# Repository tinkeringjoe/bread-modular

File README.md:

# Bread Modular
Bread Modular is an open-source hardware modular synthesizer format designed to be minimalistic and cost-effective.

### Key Features

* **Modular Design:** Just like Eurorack
* **USB-Powered:** It can be portable
* **Minimal Design:** Cost Effective
* **Modular MIDI Support:** Use MIDI to communicate between modules (still supports CV & Gate)
* **Analog and Digital Signal Paths:** It’s your choice 
* **Diverse Built-in Modules:** Includes a wide range of pre-designed modules
* **Configurable Digital Modules:** Supports both voice and CV (uses AtTiny 1616 or ESP32)
* **Fully Open Source:** Including schematics, PCB designs, and code
* **Ease of Customization:** Enables straightforward creation of custom modules tailored to specific needs.
* **No Case Required:** Can be used directly on a breadboard or mounted on a simple base module.

## Table of Contents

* [Specification](https://github.com/bread-modular/bread-modular/wiki/Specification)
* [Common Parts](https://github.com/bread-modular/bread-modular/wiki/Common-Parts)
* [Modules](https://github.com/bread-modular/bread-modular/wiki/Modules)

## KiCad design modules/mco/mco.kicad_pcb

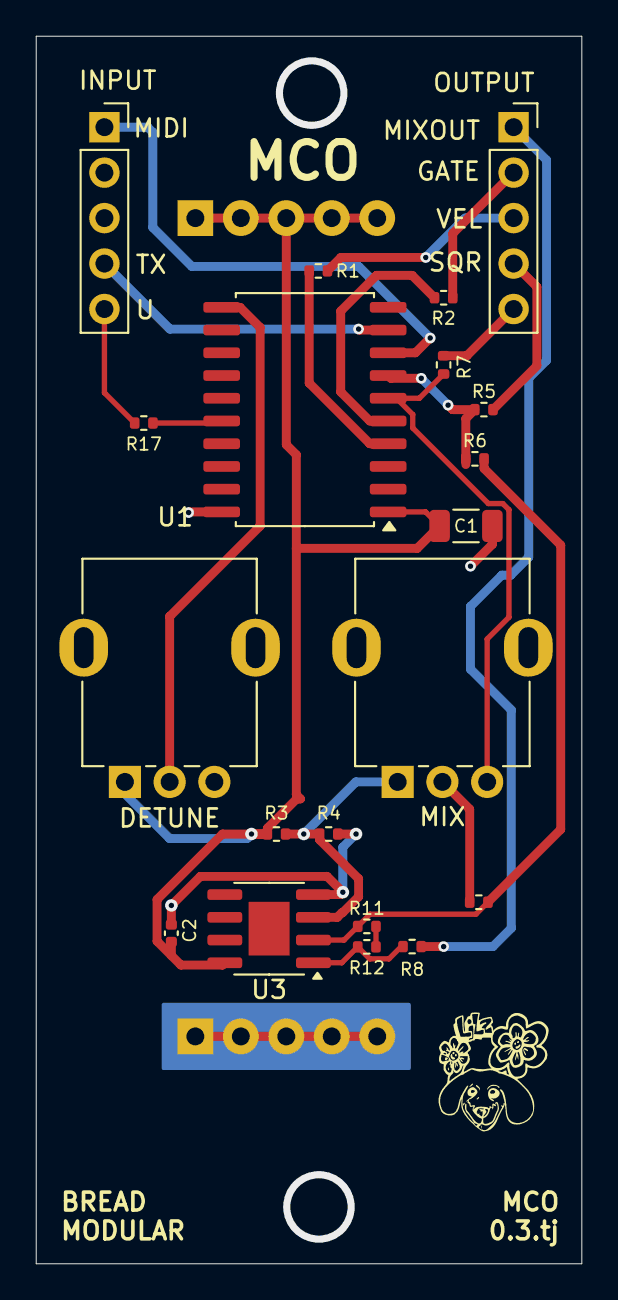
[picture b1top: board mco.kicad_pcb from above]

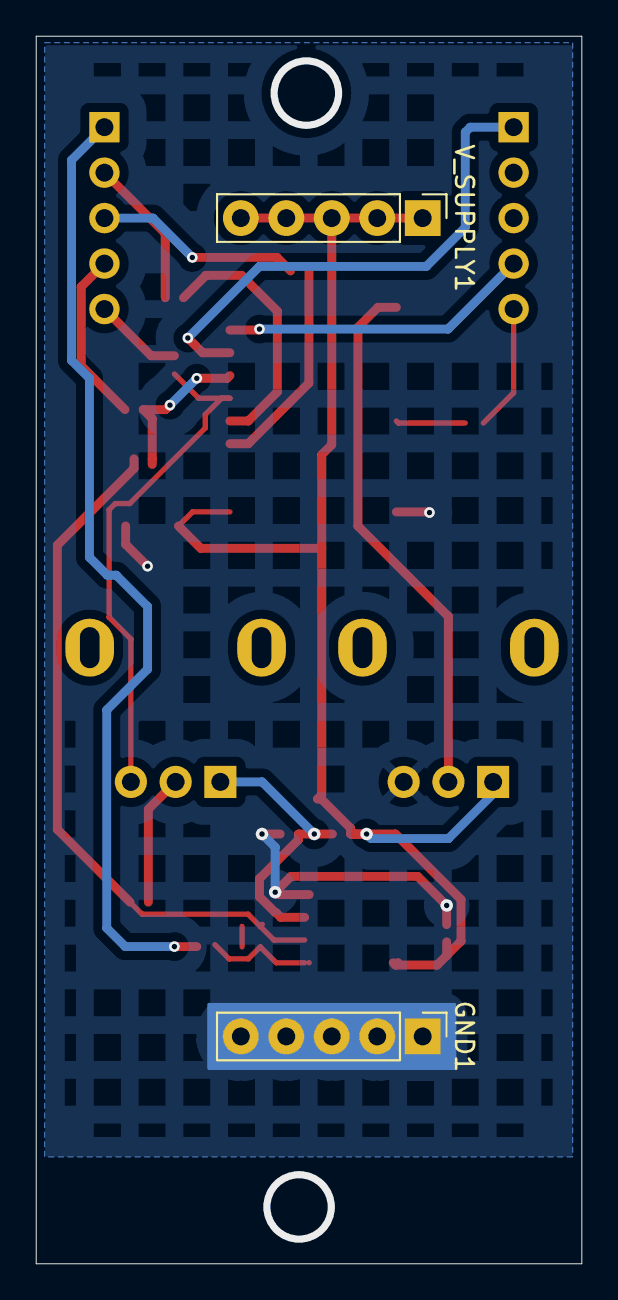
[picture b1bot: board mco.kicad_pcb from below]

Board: 2 copper layers, 30.5 x 68.6 mm, 22 parts (2 on the bottom side), 21 nets.

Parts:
C1: 100uf; C_1206_3216Metric
C2: 0.1uf; C_0402_1005Metric
GND1: Conn_01x05_Pin; Power_Connector
INPUT1: Conn_01x05_Socket; PinSocket_1x05_P2.54mm_Vertical
OUTPUT1: Conn_01x05_Socket; PinSocket_1x05_P2.54mm_Vertical
R1, R2, R3, R4, R5, R7, R8: 1k; R_0402_1005Metric
R6, R10: 1M; R_0402_1005Metric
R11, R12: 200k; R_0402_1005Metric
R17: 4.7k; R_0402_1005Metric
RV1, RV2: 50k; Potentiometer_RV09
U1: ATtiny1616-S; SOIC-20W_7.5x12.8mm_P1.27mm
U3: MCP6002-xSN; SOIC-8-1EP_3.9x4.9mm_P1.27mm_EP2.29x3mm
V_SUPPLY1: Conn_01x05_Pin; Power_Connector

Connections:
DETUNED_OUT: OUTPUT1.5, R7.2
DETUNED_TONE: R7.1, RV2.3, U1.6 (PB5)
FUNDAMENTAL_TONE: R5.1, R6.1, U1.7 (PB4)
GATE: OUTPUT1.2, R2.2
GND: C1.1, C2.2, GND1.1, GND1.2, GND1.3, GND1.4, GND1.5, R4.2, RV1.3, U1.20 (GND), U3.4 (V-)
MIDI: INPUT1.1, U1.8 (PB3)
MIX_OUT: OUTPUT1.1, R8.2
unnamed: R10.1, RV2.2
unnamed: R11.2, R12.1
unnamed: R8.1, R12.2, U3.1
unnamed: R1.1, U1.4 (PA6)
unnamed: R2.1, U1.5 (PA7)
unnamed: R17.1, U1.16 (~RESET/PA0)
unnamed: R6.2, R10.2, R11.1, U3.2 (-)
SQUARE_OUT: OUTPUT1.4, R5.2
TX: INPUT1.4, U1.9 (PB2)
UDPI: INPUT1.5, R17.2
VELOCITY: OUTPUT1.3, R1.2
V_DETUNED: RV1.2, U1.11 (PB0)
V_MID: R3.2, R4.1, RV2.1, U3.3 (+)
V_SUPPLY: C1.2, C2.1, R3.1, RV1.1, U1.1 (VCC), U3.8 (V+), V_SUPPLY1.1, V_SUPPLY1.2, V_SUPPLY1.3, V_SUPPLY1.4, V_SUPPLY1.5

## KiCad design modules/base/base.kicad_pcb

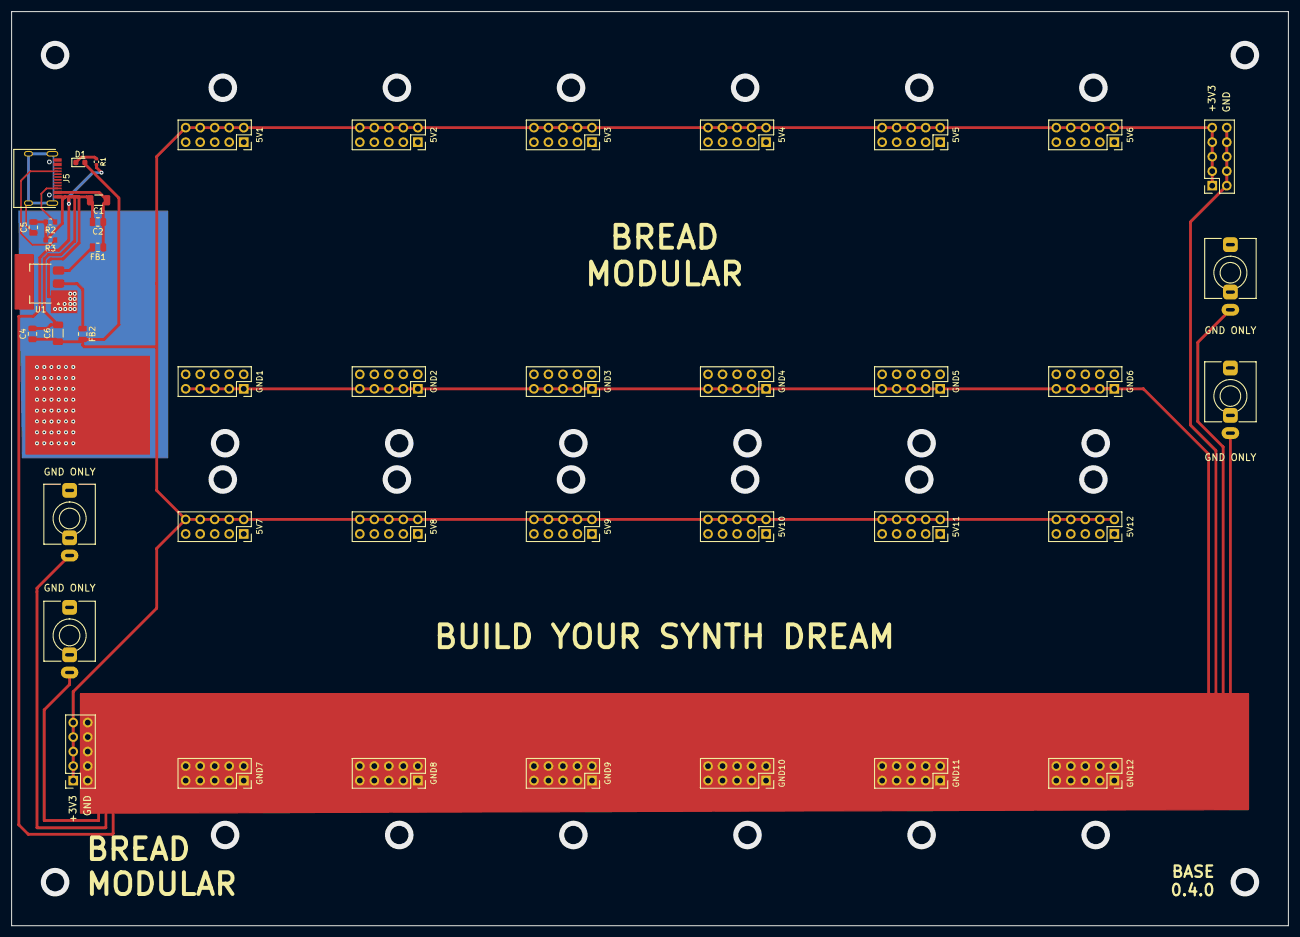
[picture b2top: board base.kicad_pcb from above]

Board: 2 copper layers, 223.5 x 160.0 mm, 43 parts (0 on the bottom side), 9 nets.

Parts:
5V1, 5V2, 5V3, 5V4, 5V5, 5V6, 5V7, 5V8, 5V9, 5V10, 5V11, 5V12, 5V13, 5V14: Conn_02x05_Socket; PinSocket_2x05_P2.54mm_Vertical
C1, C6: 100uf; C_1206_3216Metric
C2, C4: 0.1uf; C_0805_2012Metric
C5: 10nf; C_0805_2012Metric
D1: LED; LED_0603_1608Metric
FB1, FB2: GZ2012E800TF; C_0805_2012Metric
GND1, GND2, GND3, GND4, GND5, GND6, GND7, GND8, GND9, GND10, GND11, GND12: Conn_02x05_Socket; PinSocket_2x05_P2.54mm_Vertical
J1, J2, J3, J4: Ground; Jack_3.5mm_QingPu_WQP-PJ366ST_Vertical
J5: USB_C_Receptacle_PowerOnly_6P; HRO-TYPE-C-31-M-12
R1: 1k; R_0402_1005Metric
R2, R3: 5.1k; R_0603_1608Metric
U1: AMS1117-3.3; SOT-223

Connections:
+3.3V: 5V1.2, 5V1.4, 5V1.6, 5V1.8, 5V1.10, 5V2.2, 5V2.4, 5V2.6, 5V2.8, 5V2.10, 5V3.2, 5V3.4, 5V3.6, 5V3.8, 5V3.10, 5V4.2, 5V4.4, 5V4.6, 5V4.8, 5V4.10, 5V5.2, 5V5.4, 5V5.6, 5V5.8, 5V5.10, 5V6.2, 5V6.4, 5V6.6, 5V6.8, 5V6.10, 5V7.2, 5V7.4, 5V7.6, 5V7.8, 5V7.10, 5V8.2, 5V8.4, 5V8.6, 5V8.8, 5V8.10, 5V9.2, 5V9.4, 5V9.6, 5V9.8, 5V9.10, 5V10.2, 5V10.4, 5V10.6, 5V10.8, 5V10.10, 5V11.2, 5V11.4, 5V11.6, 5V11.8, 5V11.10, 5V12.2, 5V12.4, 5V12.6, 5V12.8, 5V12.10, 5V13.1, 5V13.3, 5V13.5, 5V13.7, 5V13.9, 5V14.1, 5V14.3, 5V14.5, 5V14.7, 5V14.9, C4.1, C6.1, D1.2 (A), FB2.2
+5V: C1.1, C2.1, FB1.1, J5.A9 (VBUS)
GND: 5V13.2, 5V13.4, 5V13.6, 5V13.8, 5V13.10, 5V14.2, 5V14.4, 5V14.6, 5V14.8, 5V14.10, C1.2, C2.2, C4.2, C5.2, C6.2, GND1.1, GND1.3, GND1.5, GND1.7, GND1.9, GND2.1, GND2.3, GND2.5, GND2.7, GND2.9, GND3.1, GND3.3, GND3.5, GND3.7, GND3.9, GND4.1, GND4.3, GND4.5, GND4.7, GND4.9, GND5.1, GND5.3, GND5.5, GND5.7, GND5.9, GND6.1, GND6.3, GND6.5, GND6.7, GND6.9, GND7.1, GND7.2, GND7.3, GND7.4, GND7.5, GND7.6, GND7.7, GND7.8, GND7.9, GND7.10, GND8.1, GND8.2, GND8.3, GND8.4, GND8.5, GND8.6, GND8.7, GND8.8, GND8.9, GND8.10, GND9.1, GND9.2, GND9.3, GND9.4, GND9.5, GND9.6, GND9.7, GND9.8, GND9.9, GND9.10, GND10.1, GND10.2, GND10.3, GND10.4, GND10.5, GND10.6, GND10.7, GND10.8, GND10.9, GND10.10, GND11.1, GND11.2, GND11.3, GND11.4, GND11.5, GND11.6, GND11.7, GND11.8, GND11.9, GND11.10, GND12.1, GND12.2, GND12.3, GND12.4, GND12.5, GND12.6, GND12.7, GND12.8, GND12.9, GND12.10, J1.S, J2.S, J3.S, J4.S, J5.A12 (GND), R1.2, R2.2, R3.2, U1.1 (GND)
unnamed: D1.1 (K), R1.1
unnamed: J5.A5 (CC1), R3.1
unnamed: J5.B5 (CC2), R2.1
unnamed: C5.1, J5.S1 (SHIELD)
unnamed: FB1.2, U1.3 (VI)
unnamed: FB2.1, U1.2 (VO)

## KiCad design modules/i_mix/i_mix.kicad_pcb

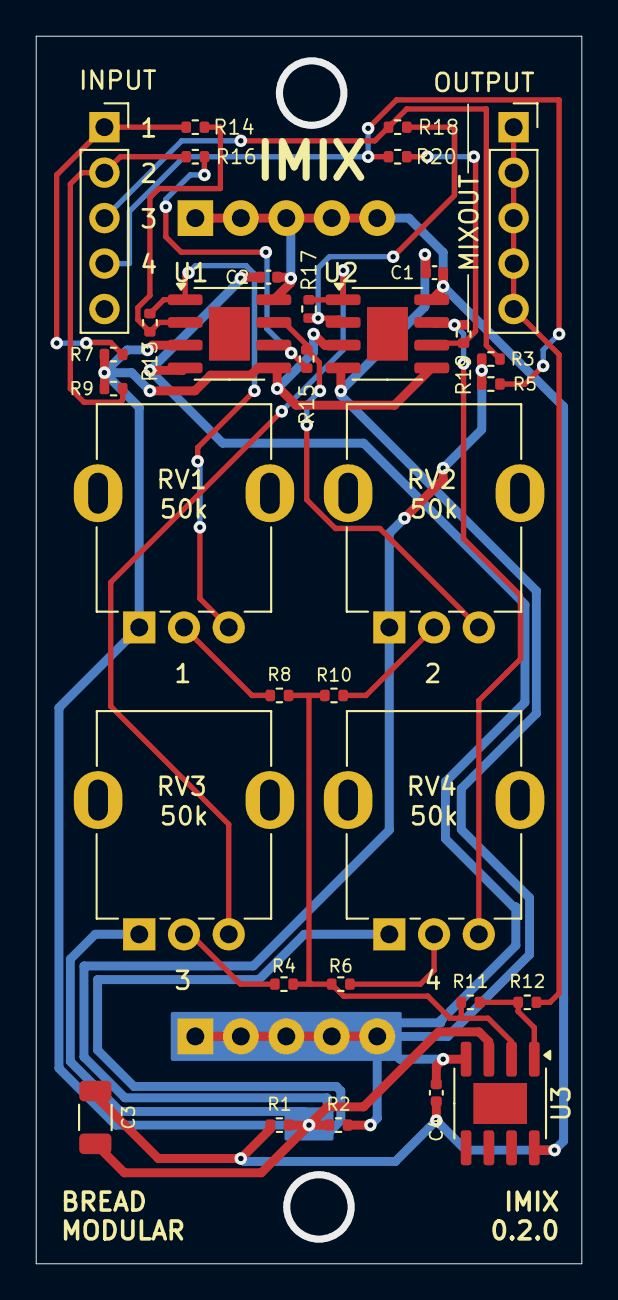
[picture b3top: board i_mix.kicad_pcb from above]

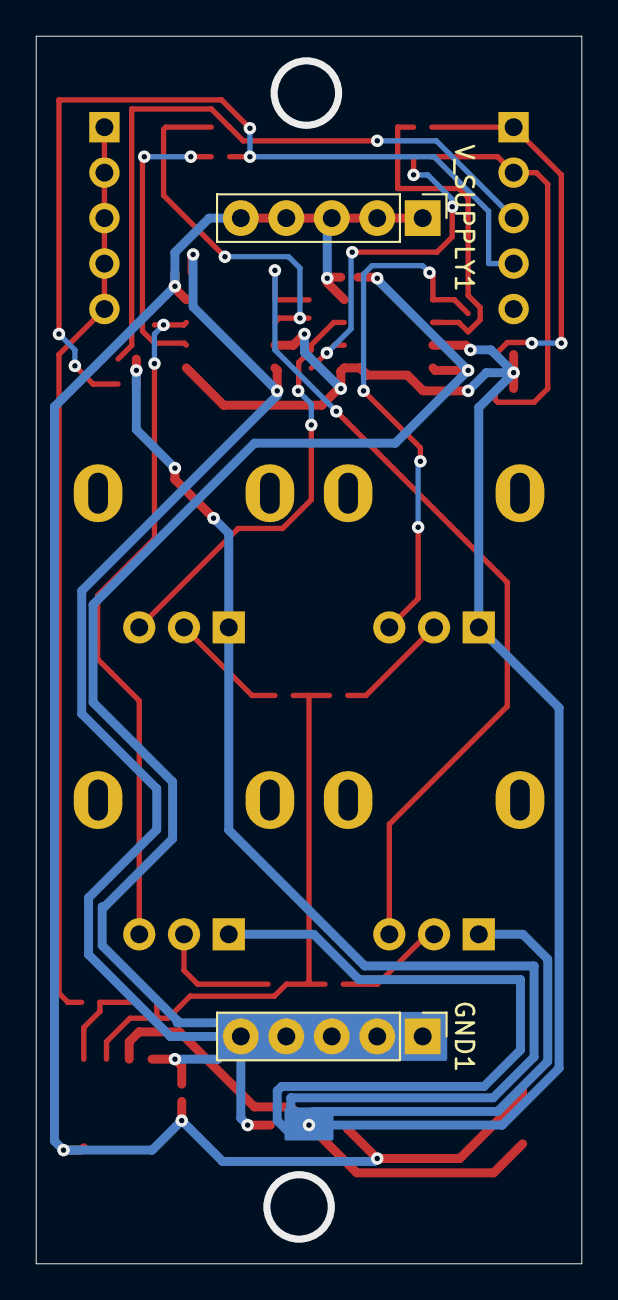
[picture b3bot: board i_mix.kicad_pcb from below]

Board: 2 copper layers, 30.5 x 68.6 mm, 35 parts (2 on the bottom side), 22 nets.

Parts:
C1, C2, C4: 0.1uf; C_0402_1005Metric
C3: 100uf; C_1206_3216Metric
GND1: Conn_01x05_Pin; Power_Connector
INPUT1: Conn_01x05_Socket; PinSocket_1x05_P2.54mm_Vertical
OUTPUT1: Conn_01x05_Socket; PinSocket_1x05_P2.54mm_Vertical
R1, R2, R12: 1k; R_0402_1005Metric
R3, R5, R7, R9: 1M; R_0402_1005Metric
R4, R6, R8, R10, R11: 200k; R_0402_1005Metric
R13, R14, R15, R16, R17, R18, R19, R20: 100k; R_0402_1005Metric
RV1, RV2, RV3, RV4: 50k; Potentiometer_RV09
U1, U2, U3: MCP6002-xSN; SOIC-8-1EP_3.9x4.9mm_P1.27mm_EP2.29x3mm
V_SUPPLY1: Conn_01x05_Pin; Power_Connector

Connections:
GND: C1.2, C2.2, C4.2, GND1.1, GND1.2, GND1.3, GND1.4, GND1.5, R2.2, U1.4 (V-), U2.4 (V-), U3.4 (V-)
IN_1: INPUT1.1, R7.2, R14.1
IN_2: INPUT1.2, R9.2, R16.1
IN_3: INPUT1.3, R3.2, R18.1
IN_4: INPUT1.4, R5.2, R20.1
MIXOUT: OUTPUT1.1, OUTPUT1.2, OUTPUT1.3, OUTPUT1.4, OUTPUT1.5, R12.2
unnamed: R4.1, RV3.2
unnamed: R6.1, RV4.2
unnamed: R8.1, RV1.2
unnamed: R10.1, RV2.2
unnamed: R11.2, R12.1, U3.1
unnamed: R13.2, RV1.3, U1.1
unnamed: R15.2, RV2.3, U1.7
unnamed: R17.2, RV3.3, U2.1
unnamed: R19.2, RV4.3, U2.7
unnamed: R13.1, R14.2, U1.2 (-)
unnamed: R15.1, R16.2, U1.6 (-)
unnamed: R17.1, R18.2, U2.2 (-)
unnamed: R19.1, R20.2, U2.6 (-)
unnamed: R4.2, R6.2, R8.2, R10.2, R11.1, U3.2 (-)
V_MID: C3.2, R1.2, R2.1, R3.1, R5.1, R7.1, R9.1, RV1.1, RV2.1, RV3.1, RV4.1, U1.3 (+), U1.5 (+), U2.3 (+), U2.5 (+), U3.3 (+)
V_SUPPLY: C1.1, C2.1, C3.1, C4.1, R1.1, U1.8 (V+), U2.8 (V+), U3.8 (V+), V_SUPPLY1.1, V_SUPPLY1.2, V_SUPPLY1.3, V_SUPPLY1.4, V_SUPPLY1.5

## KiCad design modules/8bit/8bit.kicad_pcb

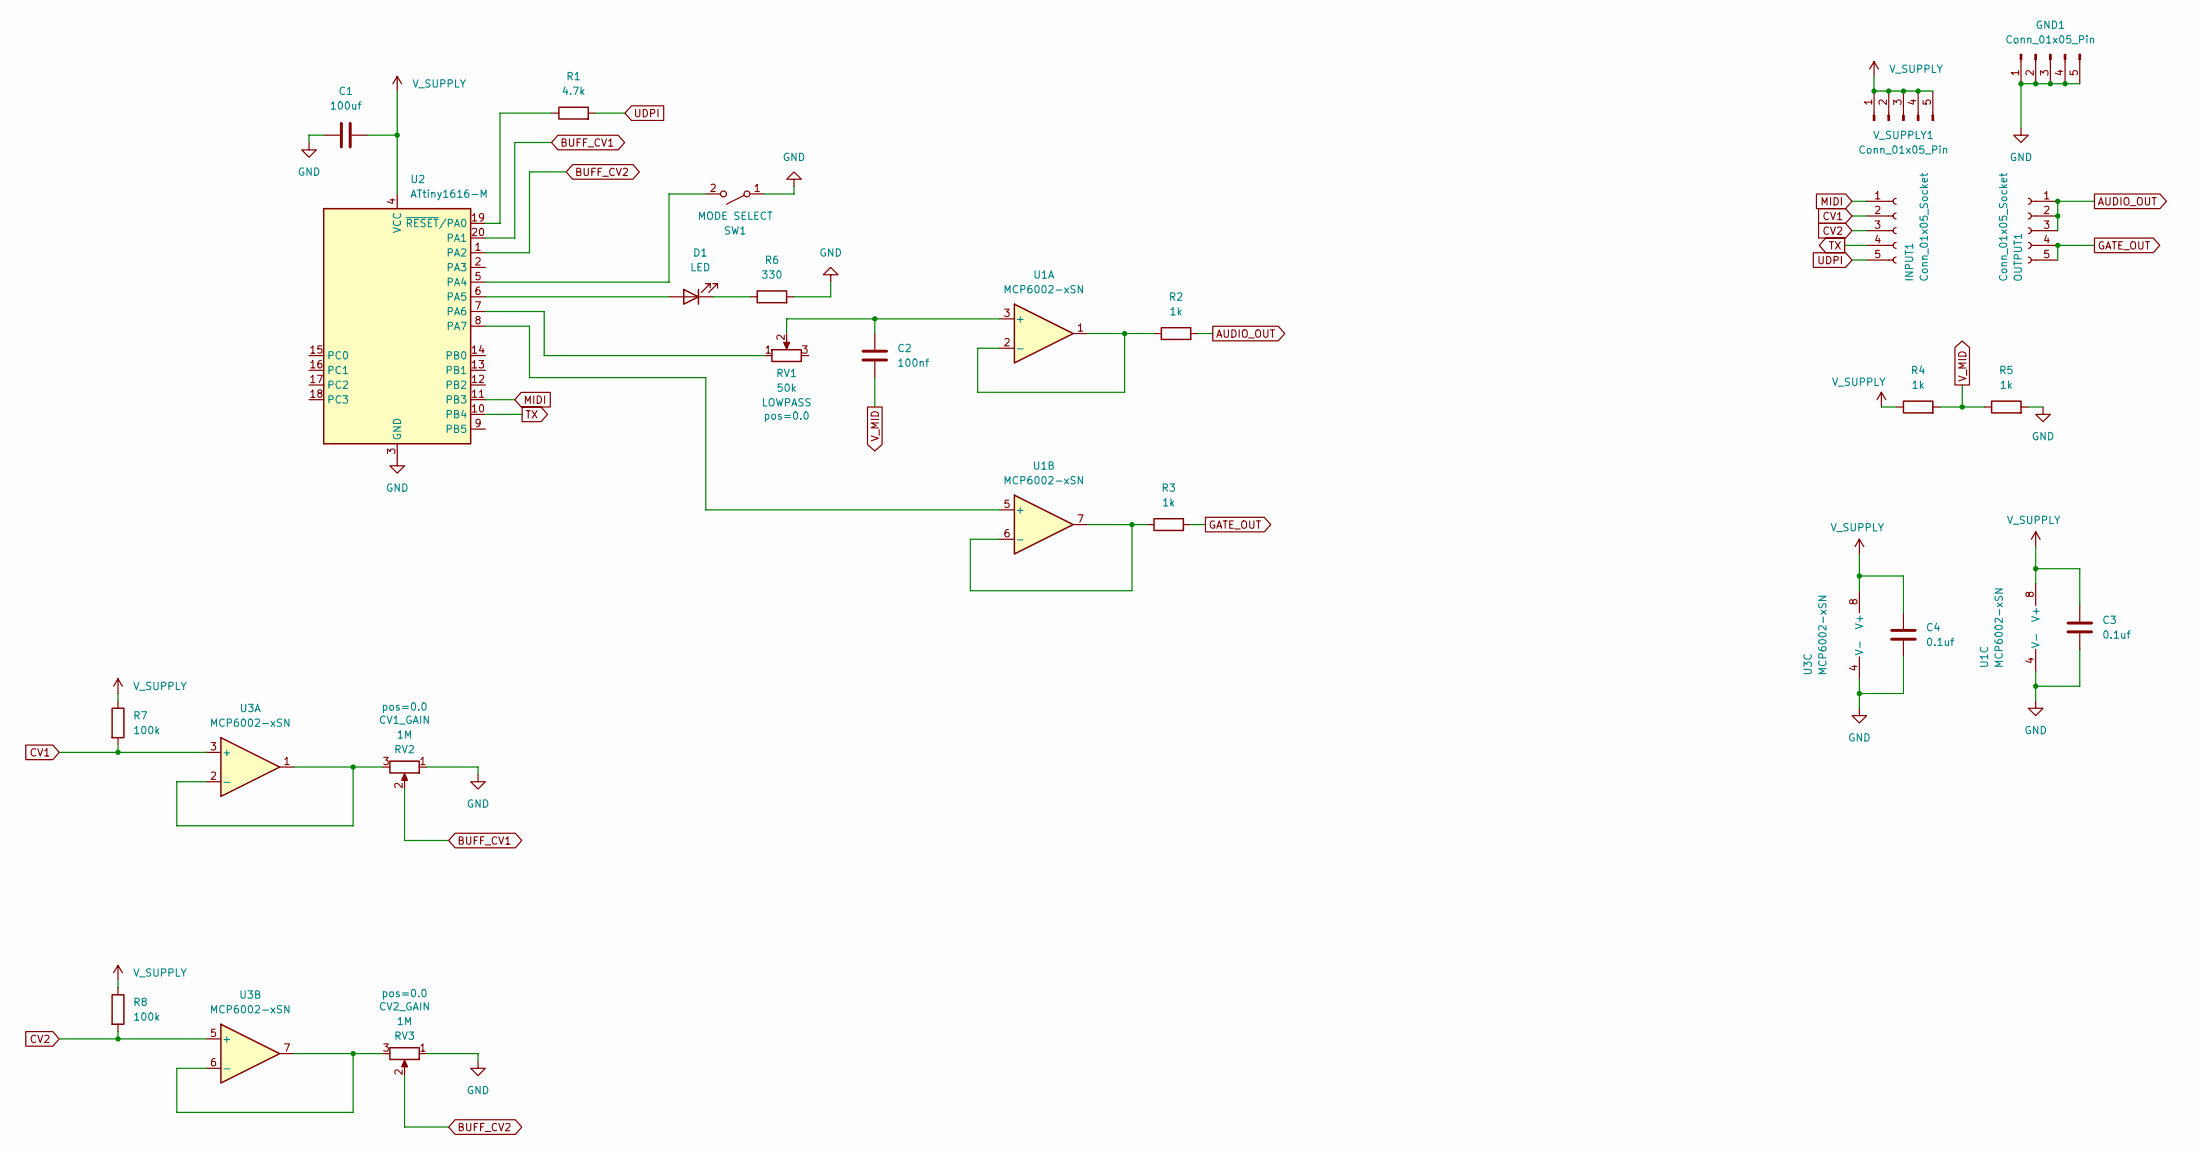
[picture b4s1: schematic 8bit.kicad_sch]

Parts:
C1: 100uf; C_1206_3216Metric
C2: 100nf; C_0402_1005Metric
C3, C4: 0.1uf; C_0402_1005Metric
D1: LED; LED_0603_1608Metric
GND1: Conn_01x05_Pin; Power_Connector
INPUT1: Conn_01x05_Socket; PinSocket_1x05_P2.54mm_Vertical
OUTPUT1: Conn_01x05_Socket; PinSocket_1x05_P2.54mm_Vertical
R1: 4.7k; R_0402_1005Metric
R2, R3, R4, R5: 1k; R_0402_1005Metric
R6: 330; R_0402_1005Metric
R7, R8: 100k; R_0402_1005Metric
RV1: 50k; Potentiometer_RV09
RV2, RV3: 1M; Potentiometer_RV09
SW1: MODE SELECT; SPST_TS-1187A-B-A-B
U1, U3: MCP6002-xSN; SOIC-8-1EP_3.9x4.9mm_P1.27mm_EP2.29x3mm
U2: ATtiny1616-M; VQFN-20-1EP_3x3mm_P0.4mm_EP1.7x1.7mm
V_SUPPLY1: Conn_01x05_Pin; Power_Connector

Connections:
AUDIO_OUT: OUTPUT1.1, OUTPUT1.2, OUTPUT1.3, R2.2
BUFF_CV1: RV2.2, U2.20 (PA1)
BUFF_CV2: RV3.2, U2.1 (PA2)
CV1: INPUT1.2, R7.2, U3.3 (+)
CV2: INPUT1.3, R8.2, U3.5 (+)
GATE_OUT: OUTPUT1.4, OUTPUT1.5, R3.2
GND: C1.1, C3.2, C4.2, GND1.1, GND1.2, GND1.3, GND1.4, GND1.5, R5.2, R6.2, RV2.1, RV3.1, SW1.1 (A), U1.4 (V-), U2.3 (GND), U2.21 (GND), U3.4 (V-)
MIDI: INPUT1.1, U2.11 (PB3)
unnamed: D1.2 (A), U2.6 (PA5)
unnamed: D1.1 (K), R6.1
unnamed: SW1.2 (B), U2.5 (PA4)
unnamed: C2.2, RV1.2, U1.3 (+)
unnamed: R2.1, U1.1, U1.2 (-)
unnamed: U1.5 (+), U2.8 (PA7)
unnamed: R3.1, U1.6 (-), U1.7
unnamed: RV1.1, U2.7 (PA6)
unnamed: R1.1, U2.19 (~RESET/PA0)
unnamed: RV2.3, U3.1, U3.2 (-)
unnamed: RV3.3, U3.6 (-), U3.7
TX: INPUT1.4, U2.10 (PB4)
UDPI: INPUT1.5, R1.2
V_MID: C2.1, R4.2, R5.1
V_SUPPLY: C1.2, C3.1, C4.1, R4.1, R7.1, R8.1, U1.8 (V+), U2.4 (VCC), U3.8 (V+), V_SUPPLY1.1, V_SUPPLY1.2, V_SUPPLY1.3, V_SUPPLY1.4, V_SUPPLY1.5

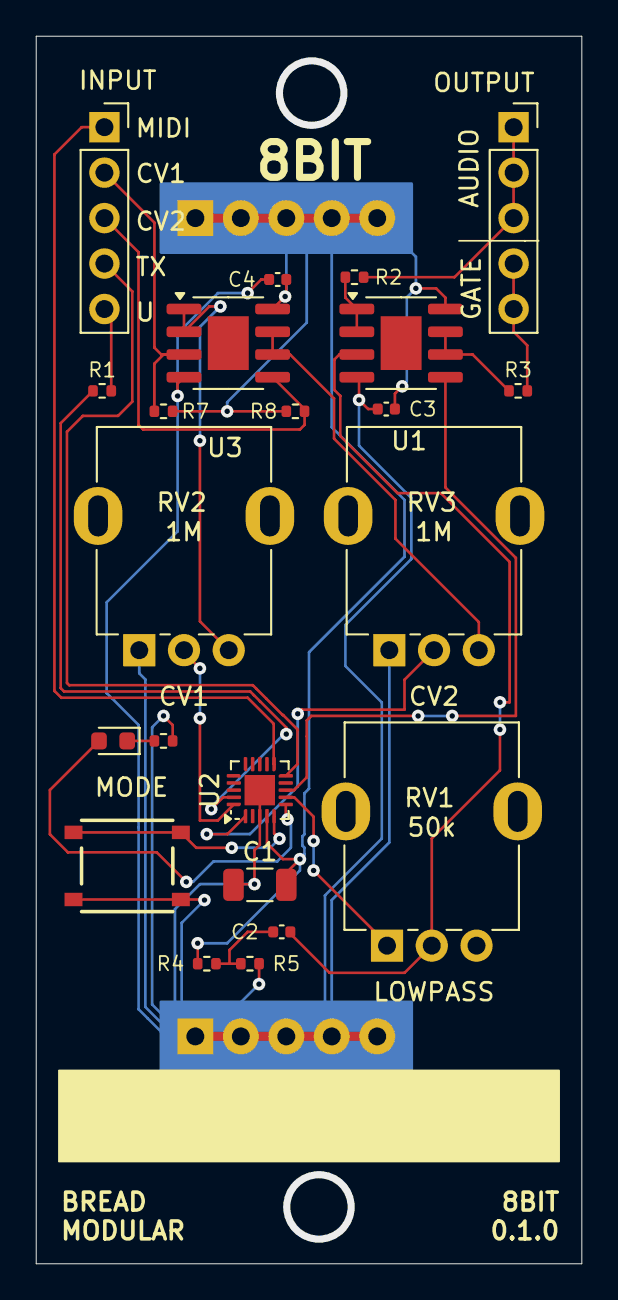
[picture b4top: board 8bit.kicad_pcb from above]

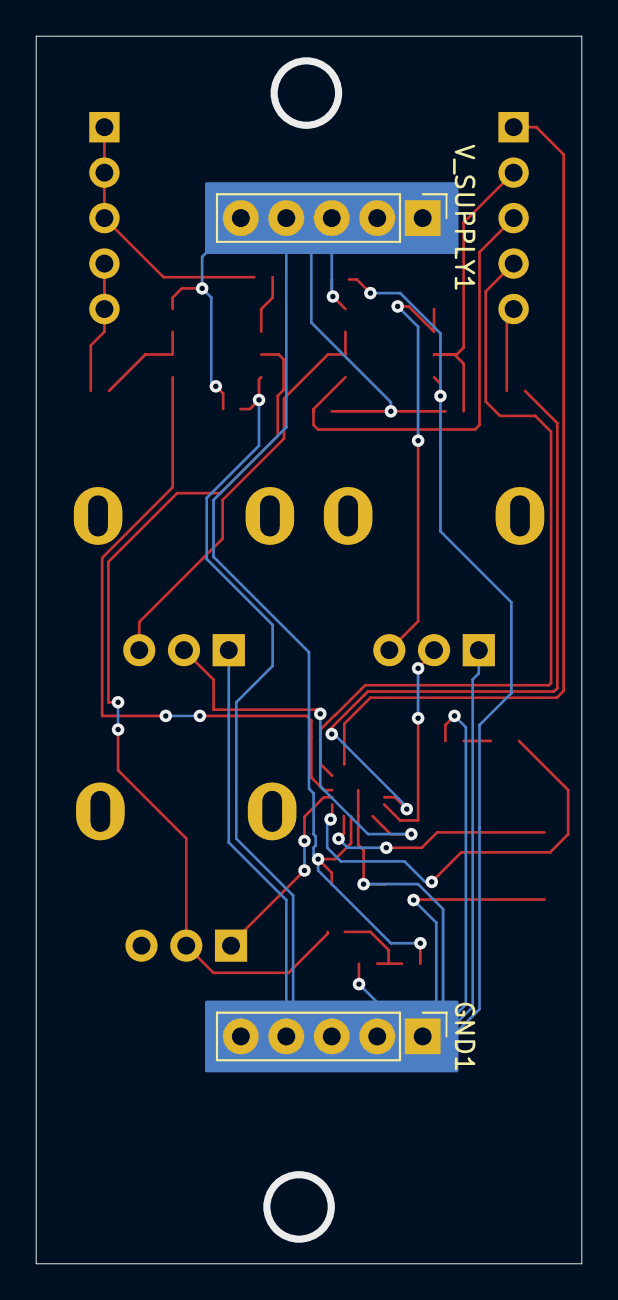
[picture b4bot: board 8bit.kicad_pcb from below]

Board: 2 copper layers, 30.5 x 68.6 mm, 24 parts (2 on the bottom side), 23 nets.

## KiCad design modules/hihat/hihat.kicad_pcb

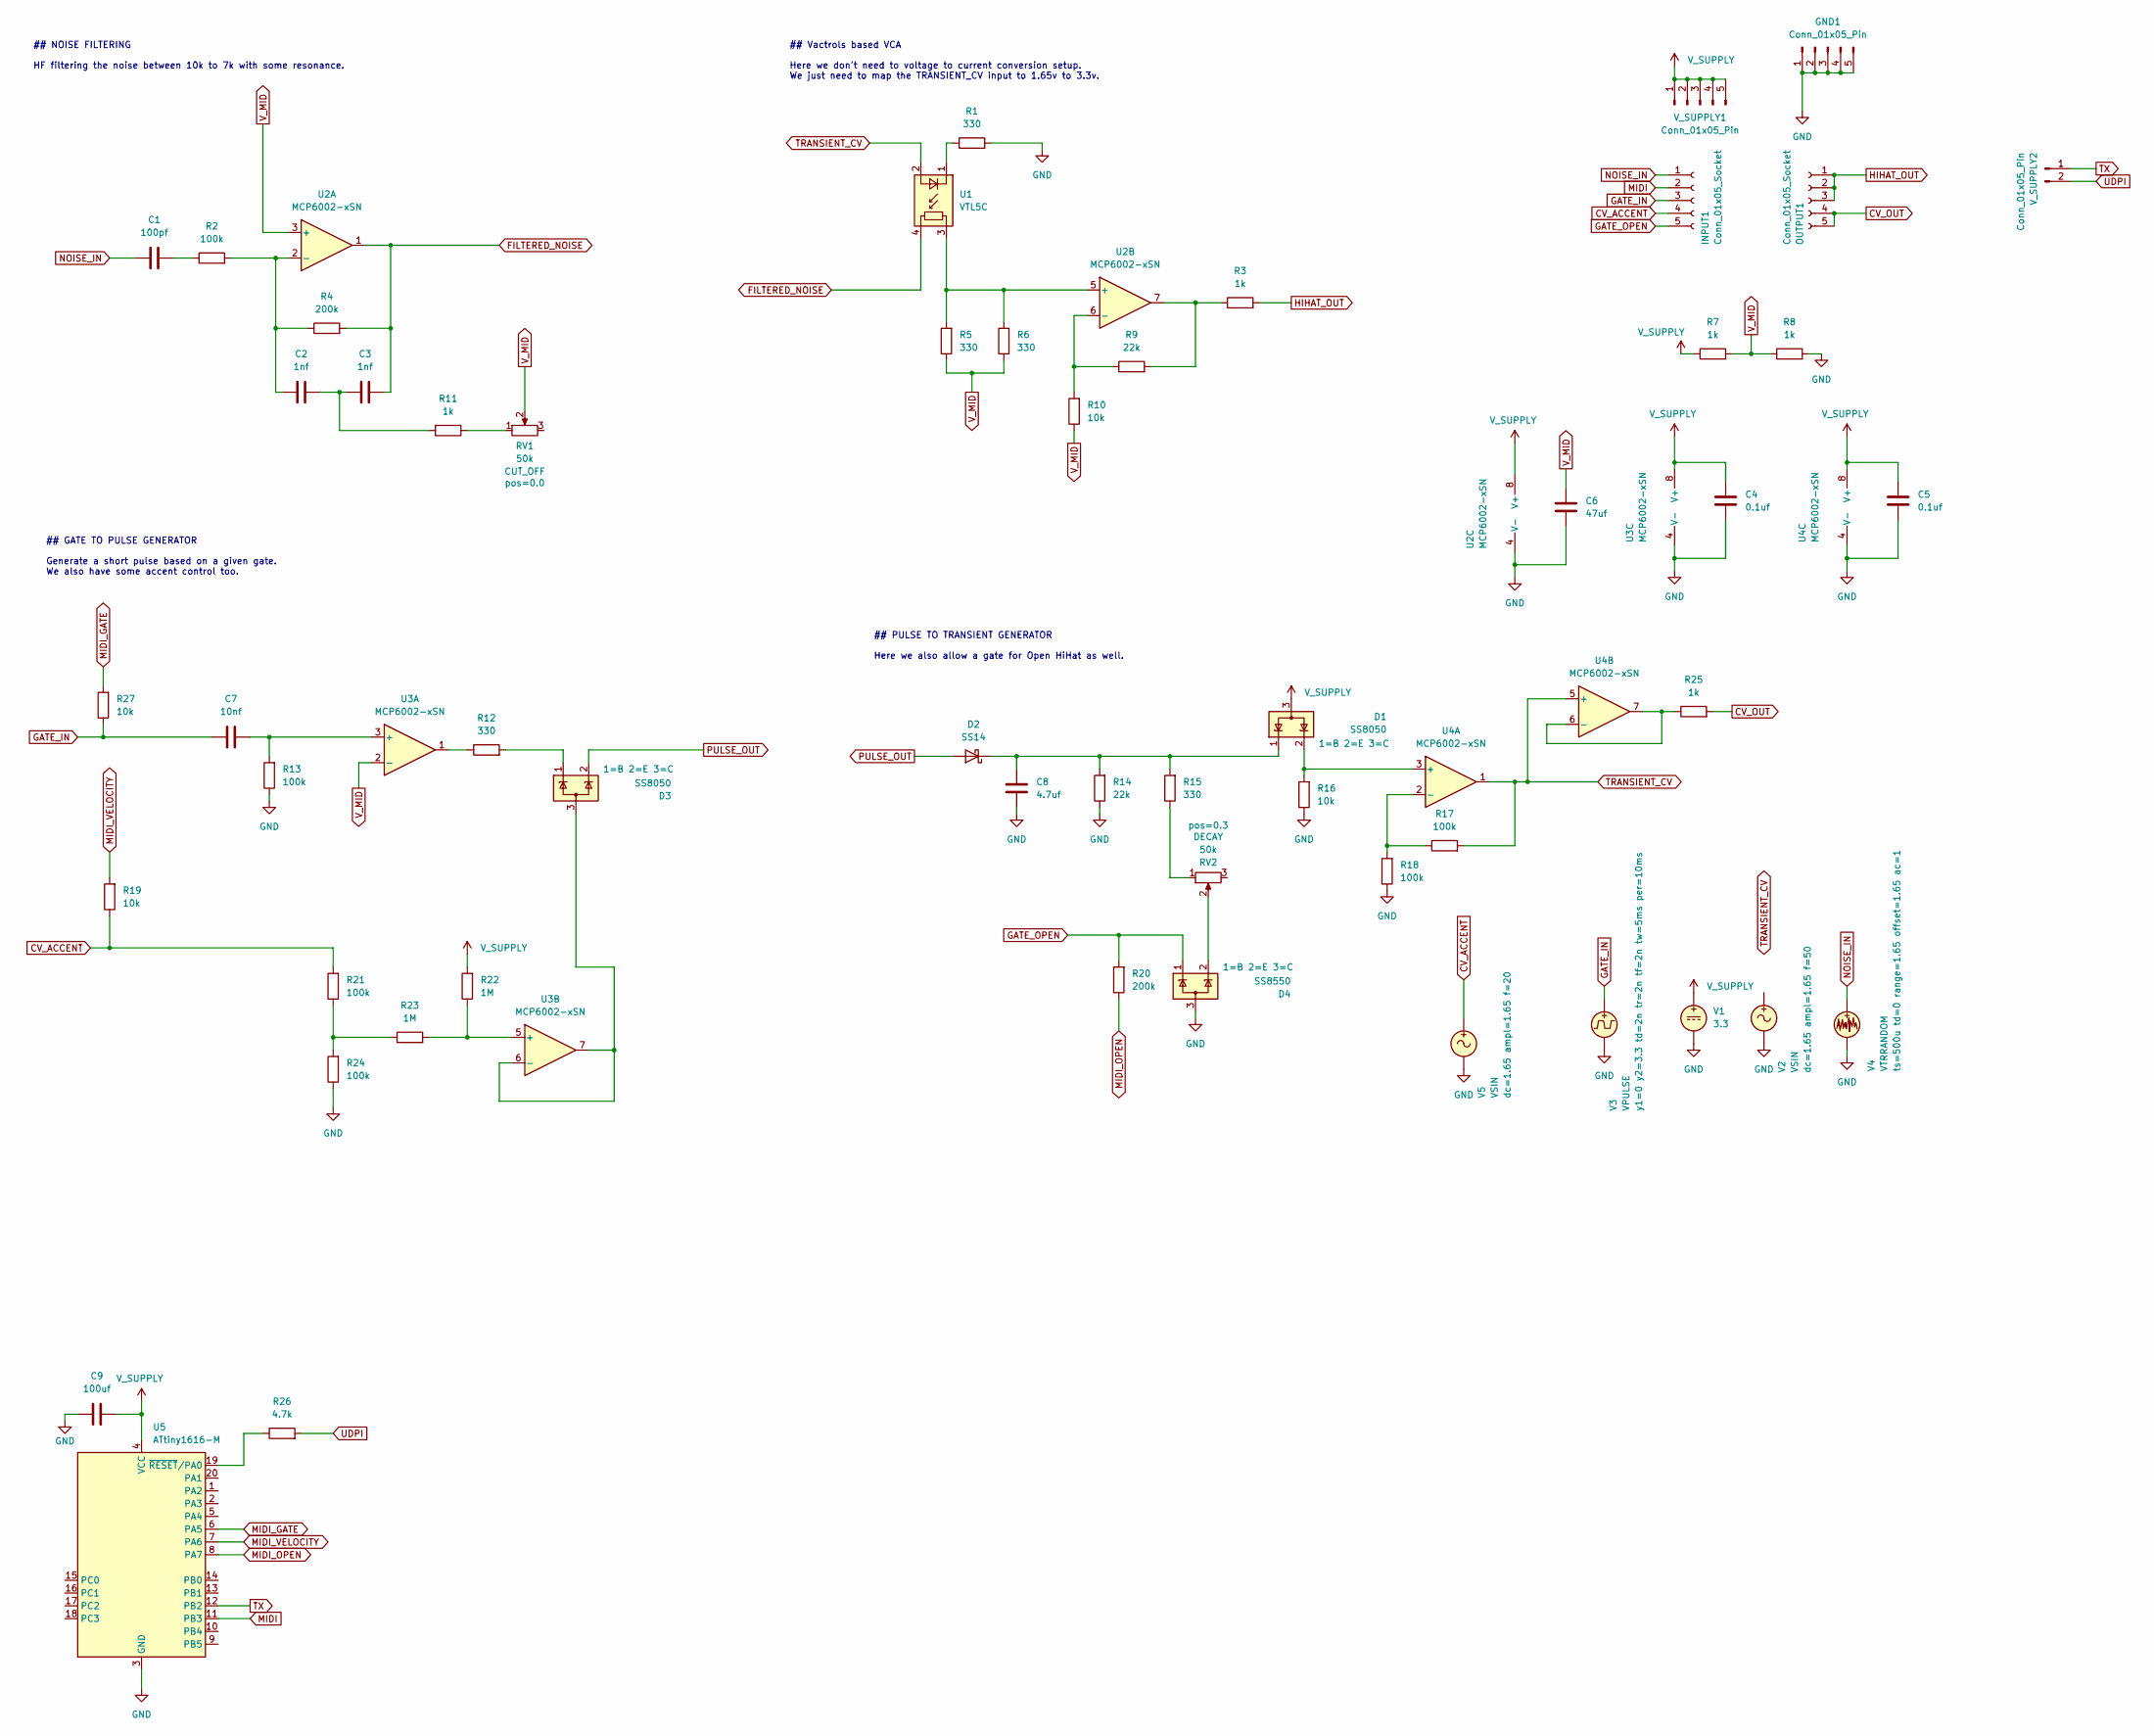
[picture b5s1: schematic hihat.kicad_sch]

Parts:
C1: 100pf; C_0402_1005Metric
C2, C3: 1nf; C_0402_1005Metric
C4, C5: 0.1uf; C_0402_1005Metric
C6: 47uf; C_0805_2012Metric
C7: 10nf; C_0402_1005Metric
C8: 4.7uf; C_0603_1608Metric
C9: 100uf; C_1206_3216Metric
D1, D3: SS8050; SOT-23
D2: SS14; D_SMA
D4: SS8550; SOT-23
GND1: Conn_01x05_Pin; Power_Connector
INPUT1: Conn_01x05_Socket; PinSocket_1x05_P2.54mm_Vertical
OUTPUT1: Conn_01x05_Socket; PinSocket_1x05_P2.54mm_Vertical
R1, R5, R6, R12, R15: 330; R_0402_1005Metric
R2, R13, R17, R18, R21, R24: 100k; R_0402_1005Metric
R3, R7, R8, R11, R25: 1k; R_0402_1005Metric
R4, R20: 200k; R_0402_1005Metric
R9, R14: 22k; R_0402_1005Metric
R10, R16, R19, R27: 10k; R_0402_1005Metric
R22, R23: 1M; R_0402_1005Metric
R26: 4.7k; R_0402_1005Metric
RV1, RV2: 50k; Potentiometer_RV09
U1: VTL5C
U2, U3, U4: MCP6002-xSN; SOIC-8-1EP_3.9x4.9mm_P1.27mm_EP2.29x3mm
U5: ATtiny1616-M; VQFN-20-1EP_3x3mm_P0.4mm_EP1.7x1.7mm
V1: 3.3
V2, V5: VSIN
V3: VPULSE
V4: VTRRANDOM
V_SUPPLY1: Conn_01x05_Pin; Power_Connector
V_SUPPLY2: Conn_01x05_Pin; Conn_Holes_2

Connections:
CV_ACCENT: INPUT1.4, R19.1, R21.2, V5.1
CV_OUT: OUTPUT1.4, OUTPUT1.5, R25.2
FILTERED_NOISE: C3.2, R4.2, U1.4, U2.1
GATE_IN: C7.1, INPUT1.3, R27.1, V3.1
GATE_OPEN: D4.1 (K), INPUT1.5, R20.2
GND: C4.1, C5.1, C6.1, C8.1, C9.1, D4.3 (A), GND1.1, GND1.2, GND1.3, GND1.4, GND1.5, R1.2, R8.2, R13.1, R14.1, R16.1, R18.1, R24.1, U2.4 (V-), U3.4 (V-), U4.4 (V-), U5.3 (GND), U5.21 (GND), V1.2, V2.2, V3.2, V4.2, V5.2
HIHAT_OUT: OUTPUT1.1, OUTPUT1.2, OUTPUT1.3, R3.2
MIDI: INPUT1.2, U5.11 (PB3)
MIDI_GATE: R27.2, U5.6 (PA5)
MIDI_OPEN: R20.1, U5.8 (PA7)
MIDI_VELOCITY: R19.2, U5.7 (PA6)
NOISE_IN: C1.1, INPUT1.1, V4.1
unnamed: C1.2, R2.1
unnamed: C2.2, C3.1, R11.2
unnamed: C8.2, D1.1 (K), D2.1 (K), R14.2, R15.2
unnamed: D3.3 (A), U3.6 (-), U3.7
unnamed: D3.1 (K), R12.2
unnamed: D4.2 (K), RV2.2
unnamed: R3.1, R9.2, U2.7
unnamed: R11.1, RV1.1
unnamed: R12.1, U3.1
unnamed: R15.1, RV2.1
unnamed: R21.1, R23.1, R24.2
unnamed: R1.1, U1.1 (-)
unnamed: C2.1, R2.2, R4.1, U2.2 (-)
unnamed: R5.2, R6.2, U1.3, U2.5 (+)
unnamed: R9.1, R10.2, U2.6 (-)
unnamed: C7.2, R13.2, U3.3 (+)
unnamed: R22.1, R23.2, U3.5 (+)
unnamed: D1.2 (K), R16.2, U4.3 (+)
unnamed: R17.1, R18.2, U4.2 (-)
unnamed: R25.1, U4.6 (-), U4.7
unnamed: R26.1, U5.19 (~RESET/PA0)
PULSE_OUT: D2.2 (A), D3.2 (K)
TRANSIENT_CV: R17.2, U1.2 (+), U4.1, U4.5 (+)
TX: U5.12 (PB2), V_SUPPLY2.1
UDPI: R26.2, V_SUPPLY2.2
V_MID: C6.2, R5.1, R6.1, R7.2, R8.1, R10.1, RV1.2, U2.3 (+), U3.2 (-)
V_SUPPLY: C4.2, C5.2, C9.2, D1.3 (A), R7.1, R22.2, U2.8 (V+), U3.8 (V+), U4.8 (V+), U5.4 (VCC), V1.1, V_SUPPLY1.1, V_SUPPLY1.2, V_SUPPLY1.3, V_SUPPLY1.4, V_SUPPLY1.5

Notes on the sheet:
## NOISE FILTERING HF filtering the noise between 10k to 7k with some resonance.
## Vactrols based VCA Here we don't need to voltage to current conversion setup. We just need to map the TRANSIENT_CV input to 1.65v to 3.3v.
## GATE TO PULSE GENERATOR Generate a short pulse based on a given gate. We also have some accent control too.
## PULSE TO TRANSIENT GENERATOR Here we also allow a gate for Open HiHat as well.

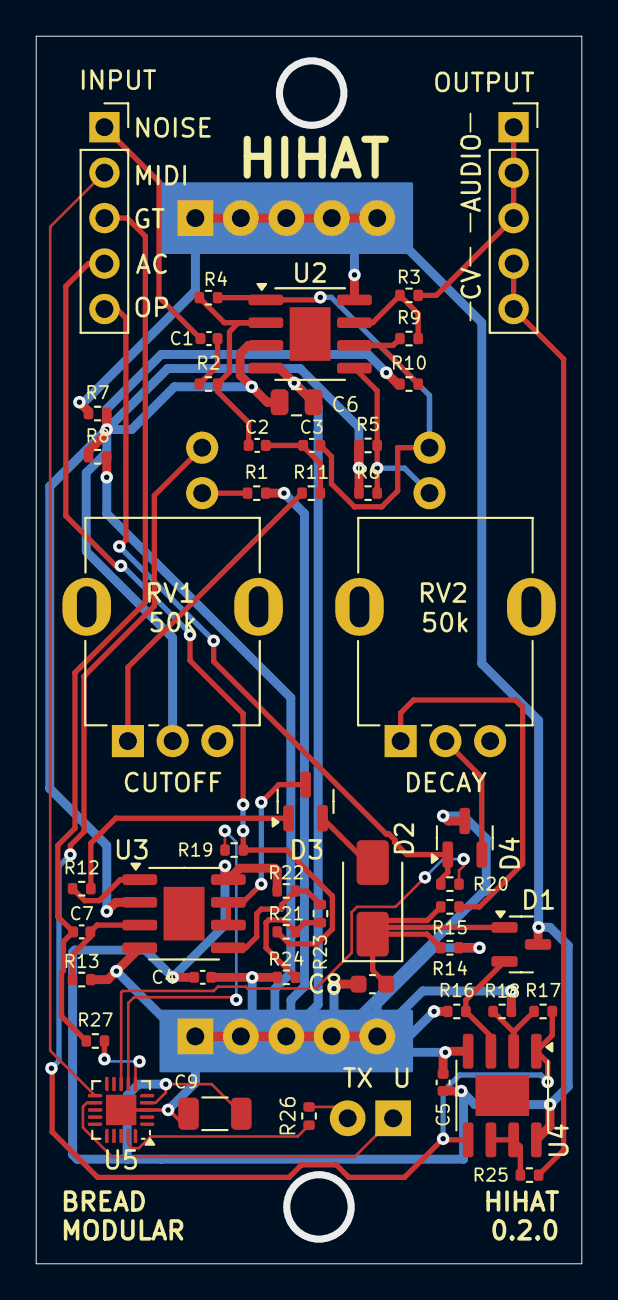
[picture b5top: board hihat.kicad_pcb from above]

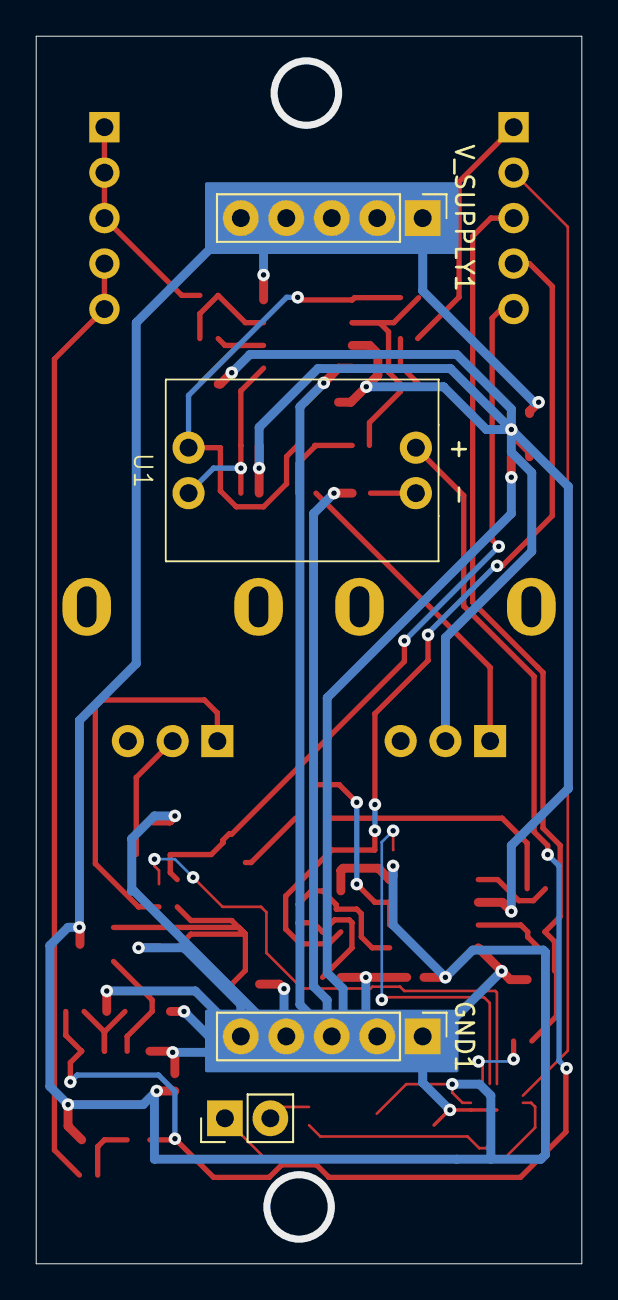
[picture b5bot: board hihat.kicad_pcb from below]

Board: 2 copper layers, 30.5 x 68.6 mm, 52 parts (4 on the bottom side), 39 nets.
